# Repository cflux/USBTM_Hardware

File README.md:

# USBTM_Hardware
Schematic for the USB Thermal Monitor

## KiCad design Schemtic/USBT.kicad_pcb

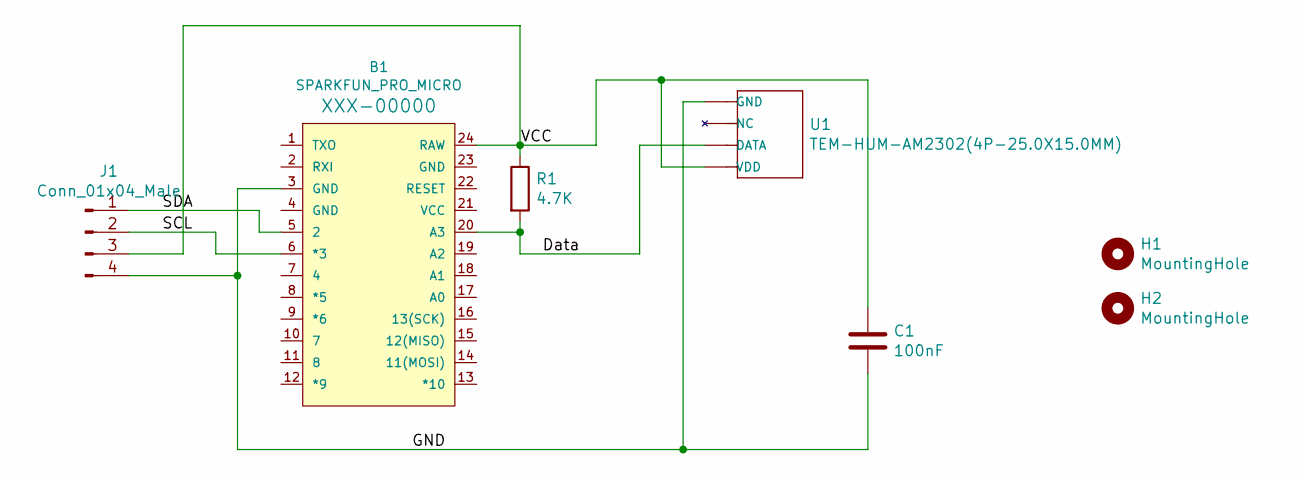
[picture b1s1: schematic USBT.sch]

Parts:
B1: SPARKFUN_PRO_MICRO
C1: 100nF; 0603
H1, H2: MountingHole; MountingHole_2.7mm_M2.5
J1: Conn_01x04_Male; PinHeader_1x04_P2.54mm_Vertical
R1: 4.7K; 0603
U1: TEM-HUM-AM2302(4P-25.0X15.0MM); SNR4-2.54-25.0X15.0X7.0MM

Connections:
/Data: B1.20 (A3), R1.2, U1.P$2 (DATA)
/GND: B1.3 (GND), C1.2, J1.4, U1.P$4 (GND)
/SCL: B1.6 (*3), J1.2
/SDA: B1.5 (2), J1.1
/VCC: B1.24 (RAW), C1.1, J1.3, R1.1, U1.P$1 (VDD)

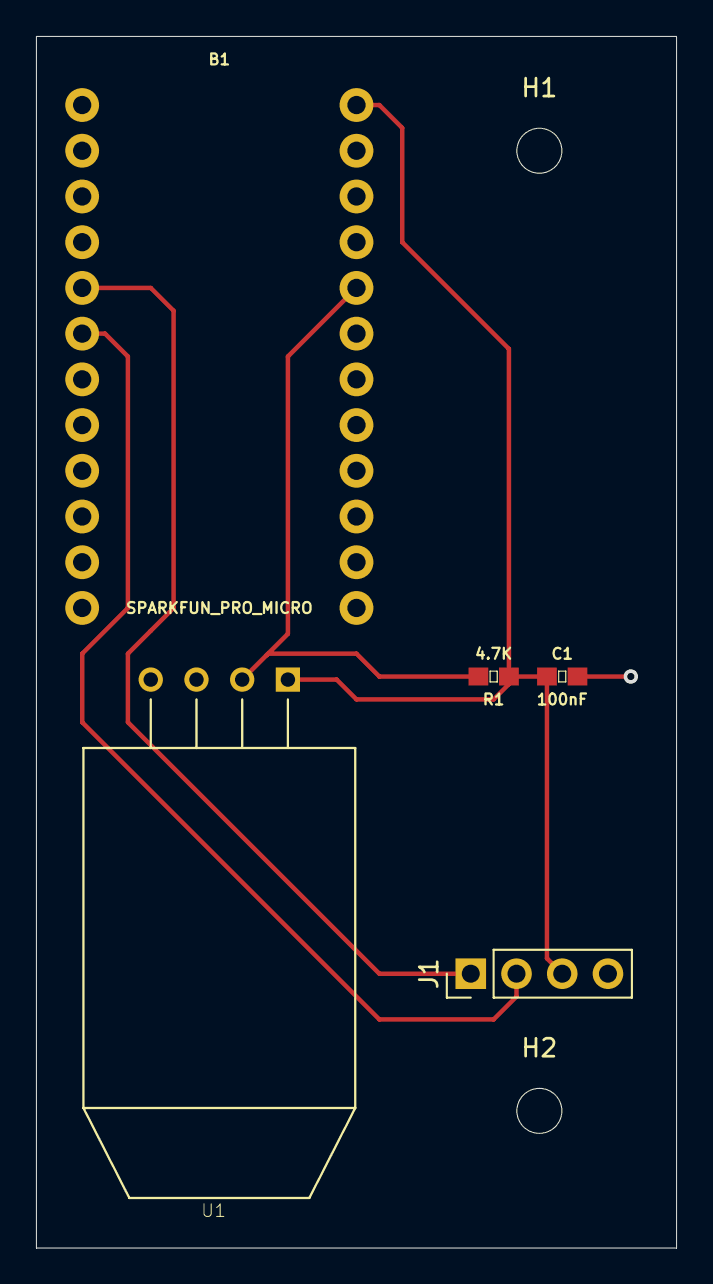
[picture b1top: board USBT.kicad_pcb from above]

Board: 2 copper layers, 35.6 x 67.3 mm, 7 parts (0 on the bottom side), 5 nets.

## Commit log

2020-07-12 V1 Hardware Checkin
2020-07-12 added stl files
